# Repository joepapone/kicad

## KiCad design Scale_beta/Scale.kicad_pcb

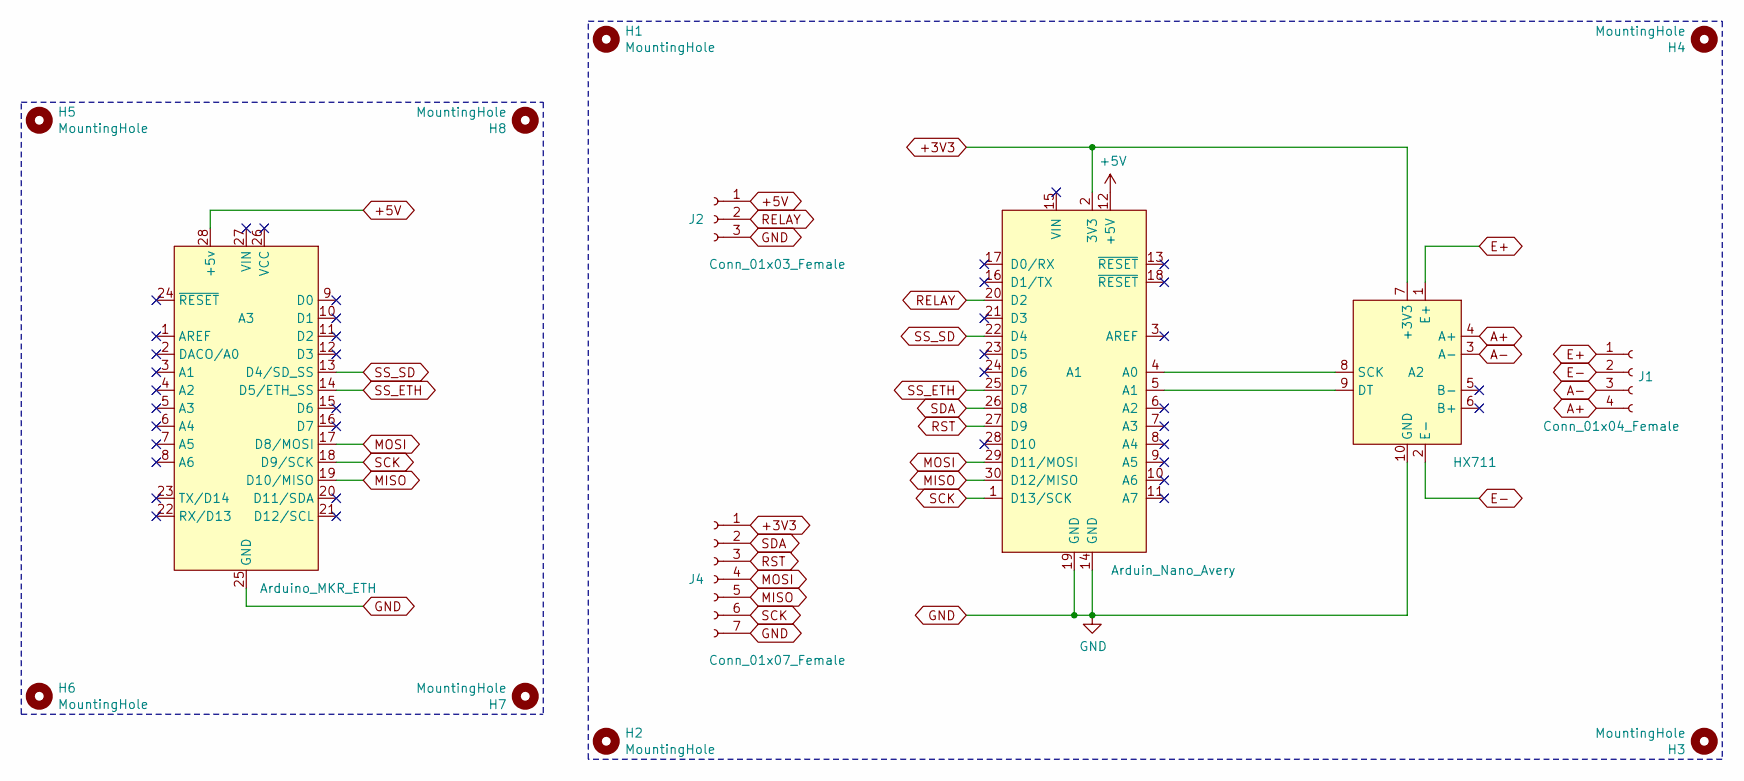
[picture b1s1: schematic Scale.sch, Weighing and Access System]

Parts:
A1: Arduin_Nano_Avery; Arduino_Nano_Every
A2: HX711; HX711_Module
A3: Arduino_MKR_ETH; MKR_ETH_Shield
H1, H2, H3, H4, H5, H6, H7, H8: MountingHole; MountingHole_2.2mm_M2
J1: Conn_01x04_Female; PinSocket_1x04_P2.54mm_Vertical
J2: Conn_01x03_Female; PinSocket_1x03_P2.54mm_Vertical
J4: Conn_01x07_Female; PinSocket_1x07_P2.54mm_Vertical

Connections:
+3V3: A1.2 (3V3), A2.7 (+3V3), J4.1
+5V: A1.12 (+5V), A3.28 (+5v), J2.1
A+: A2.4 (A+), J1.4
A-: A2.3 (A-), J1.3
E+: A2.1 (E+), J1.1
E-: A2.2 (E-), J1.2
GND: A1.14 (GND), A1.19 (GND), A2.10 (GND), A3.25 (GND), J2.3, J4.7
MISO: A1.30 (D12/MISO), A3.19 (D10/MISO), J4.5
MOSI: A1.29 (D11/MOSI), A3.17 (D8/MOSI), J4.4
unnamed: A1.4 (A0), A2.8 (SCK)
unnamed: A1.5 (A1), A2.9 (DT)
RELAY: A1.20 (D2), J2.2
RST: A1.27 (D9), J4.3
SCK: A1.1 (D13/SCK), A3.18 (D9/SCK), J4.6
SDA: A1.26 (D8), J4.2
SS_ETH: A1.25 (D7), A3.14 (D5/ETH_SS)
SS_SD: A1.22 (D4), A3.13 (D4/SD_SS)

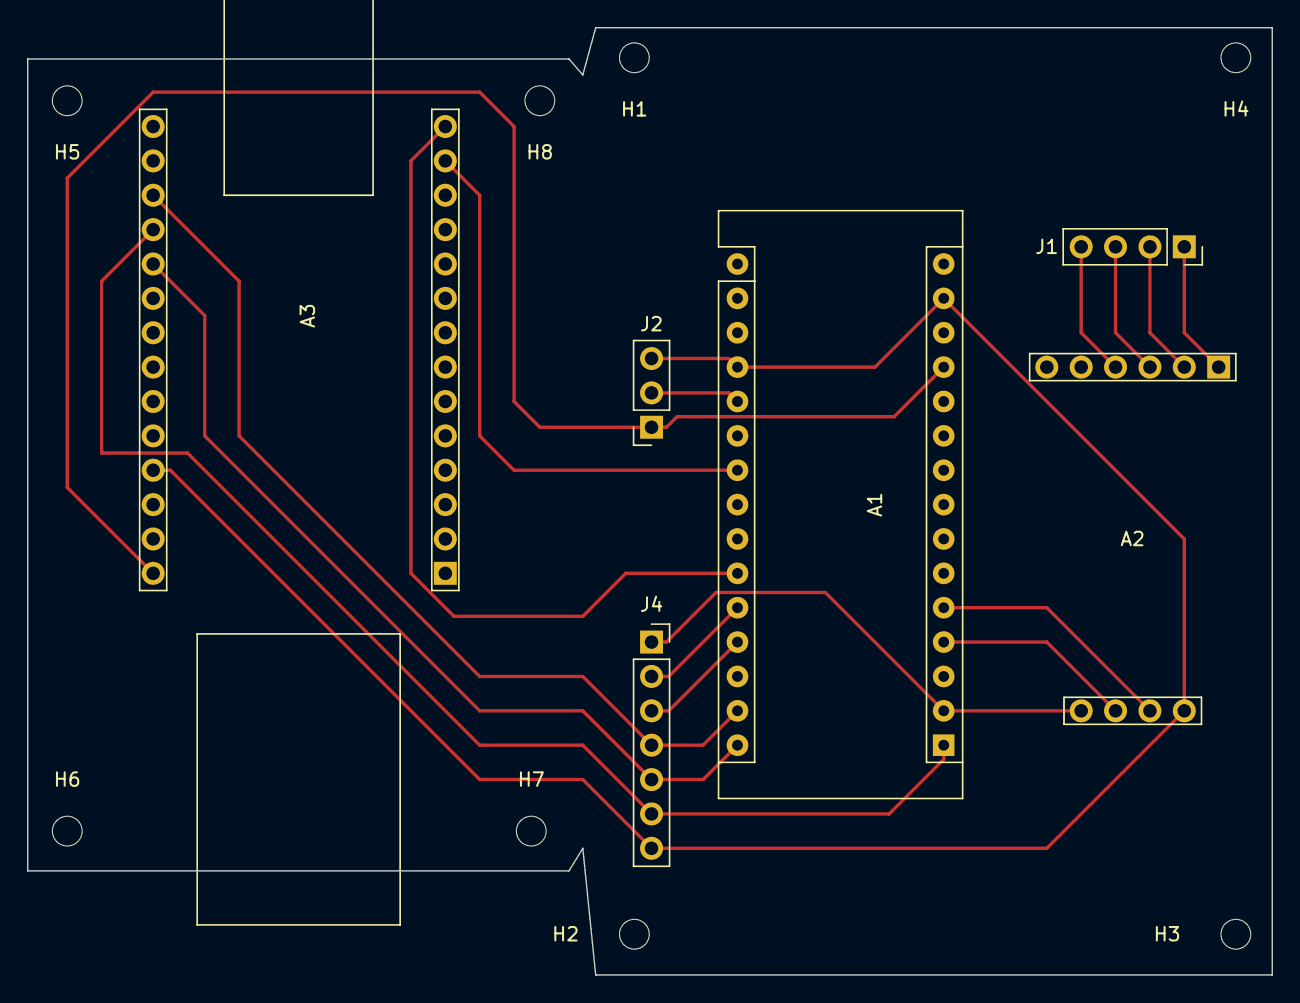
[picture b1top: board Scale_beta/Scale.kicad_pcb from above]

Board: 2 copper layers, 92.0 x 70.0 mm, 14 parts (0 on the bottom side), 17 nets.

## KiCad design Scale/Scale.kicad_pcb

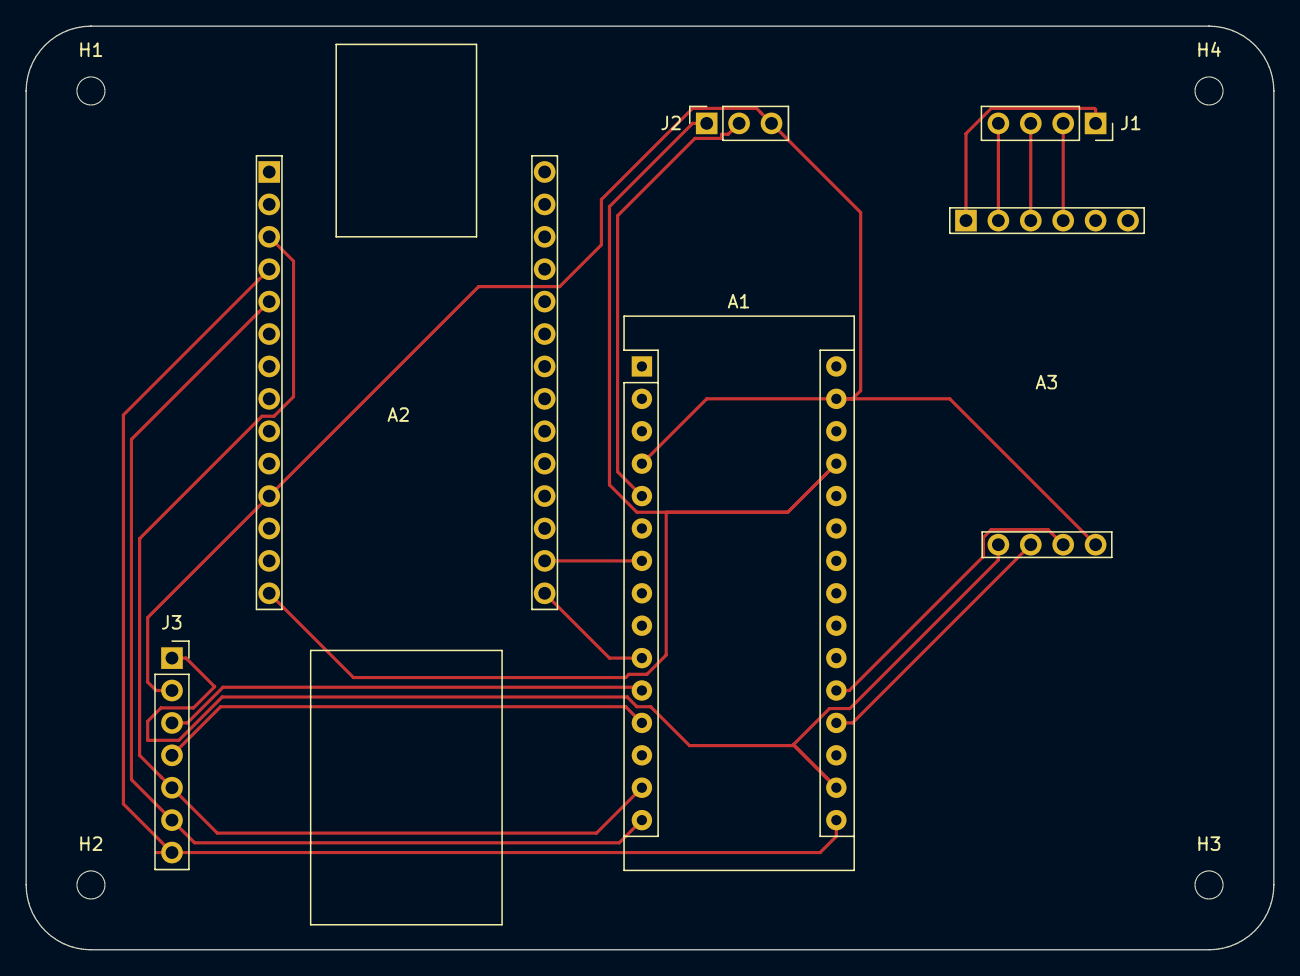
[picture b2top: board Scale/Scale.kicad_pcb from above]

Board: 2 copper layers, 97.8 x 72.4 mm, 10 parts (0 on the bottom side), 17 nets.

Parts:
A1: Arduino_Nano_v3.x; Arduino_Nano
A2: Arduino_MKR_ETH; MKR_ETH_Shield
A3: HX711; HX711_Module
H1, H2, H3, H4: MountingHole_2.2mm_M2
J1: Conn_01x04_Female; PinSocket_1x04_P2.54mm_Vertical
J2: Conn_01x03_Female; PinSocket_1x03_P2.54mm_Vertical
J3: Conn_01x07_Female; PinSocket_1x07_P2.54mm_Vertical

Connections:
GND: A1.4, A1.29, A2.11, A3.10, J2.3, J3.2
unnamed: A1.5, J2.2
unnamed: A1.7, A2.27
unnamed: A1.10, A2.28
unnamed: A1.11, J3.3
unnamed: A1.12, J3.4
unnamed: A1.14, A2.3, J3.5
unnamed: A1.15, A2.5, J3.6
unnamed: A1.16, A2.4, J3.7
unnamed: A1.17, A3.7, J3.1
unnamed: A1.19, A3.8
unnamed: A1.20, A3.9
unnamed: A1.27, A2.14, J2.1
unnamed: A3.1, J1.1
unnamed: A3.2, J1.4
unnamed: A3.3, J1.3
unnamed: A3.4, J1.2

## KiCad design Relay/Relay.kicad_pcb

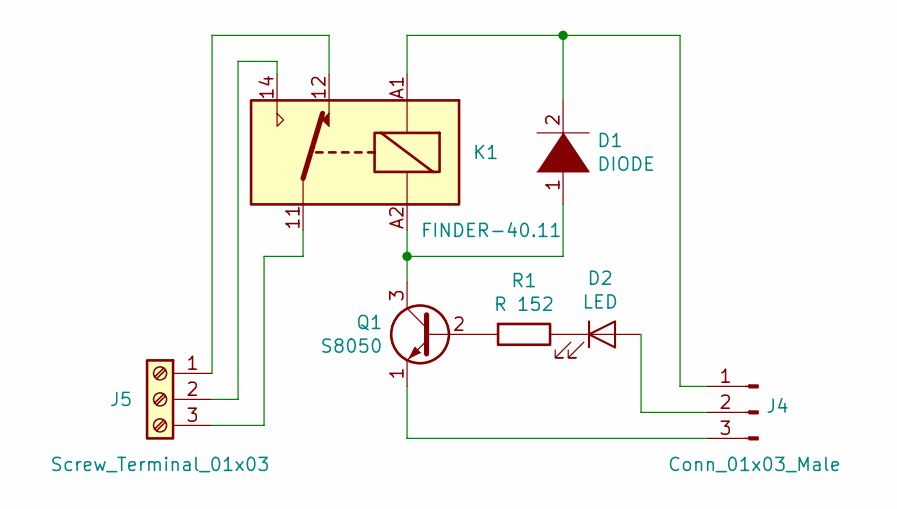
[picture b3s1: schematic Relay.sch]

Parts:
D1: DIODE; D_2010_5025Metric
D2: LED; LED_1206_3216Metric
J4: Conn_01x03_Male; PinHeader_1x03_P2.54mm_Horizontal
J5: Screw_Terminal_01x03; TerminalBlock_Phoenix_MKDS-1,5-3-5.08_1x03_P5.08mm_Horizont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
K1: FINDER-40.11; Relay_SPDT_Finder_40.11
Q1: S8050; SOT-23
R1: R 152; R_1206_3216Metric

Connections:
unnamed: D1.1 (K), K1.A2, Q1.3 (C)
unnamed: D1.2 (A), J4.1, K1.A1
unnamed: D2.1 (K), R1.1
unnamed: D2.2 (A), J4.2
unnamed: J4.3, Q1.1 (E)
unnamed: J5.1, K1.12
unnamed: J5.2, K1.14
unnamed: J5.3, K1.11
unnamed: Q1.2 (B), R1.2

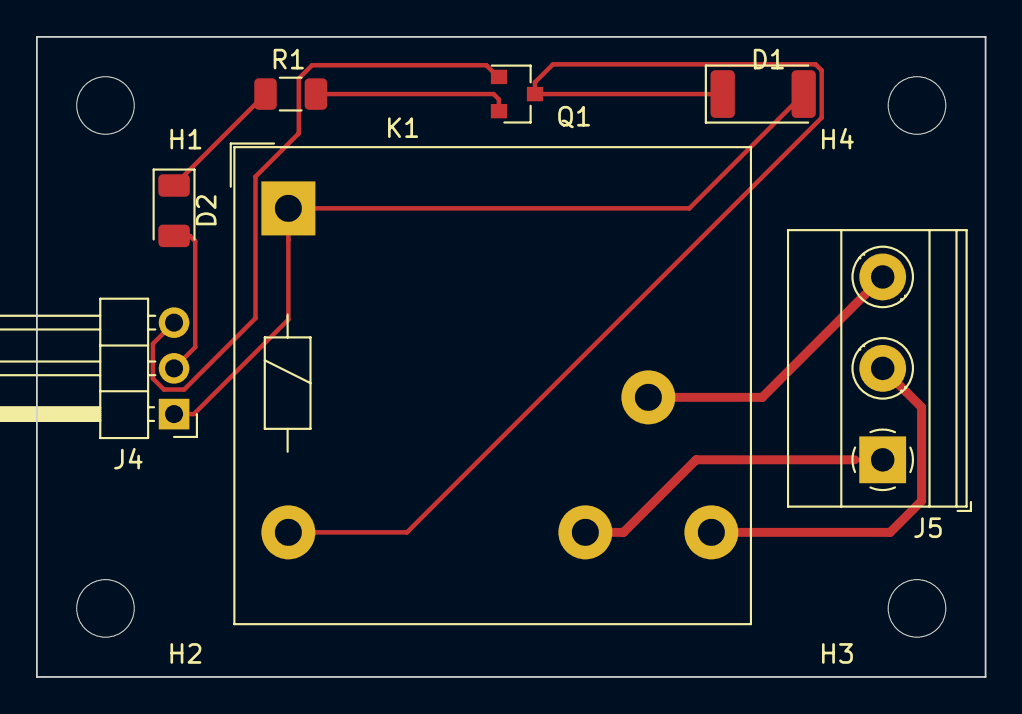
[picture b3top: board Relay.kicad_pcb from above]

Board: 2 copper layers, 52.7 x 35.6 mm, 11 parts (0 on the bottom side), 9 nets.

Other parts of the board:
H1, H2, H3, H4: MountingHole_3.2mm_M3

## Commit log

2022-07-23 Beta version
